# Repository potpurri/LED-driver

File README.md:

# LED Driver Board

This PCB is designed drive and dim the LED light in my hallway. It uses a LM2596 to step down the voltage from the  LED light adapter to dirve the circuit. The board also has a AMS1117-3.3 to step down the voltage to 3.3 V to be able to have an ESP-01 to turn on/off the LEDS.

## Images

### Schematic

### 3D Renderings
- Front View: 
- Back View: 

### PCB
**2-Layer Stackup**: Signal Layer, GND Layer
- All layers:

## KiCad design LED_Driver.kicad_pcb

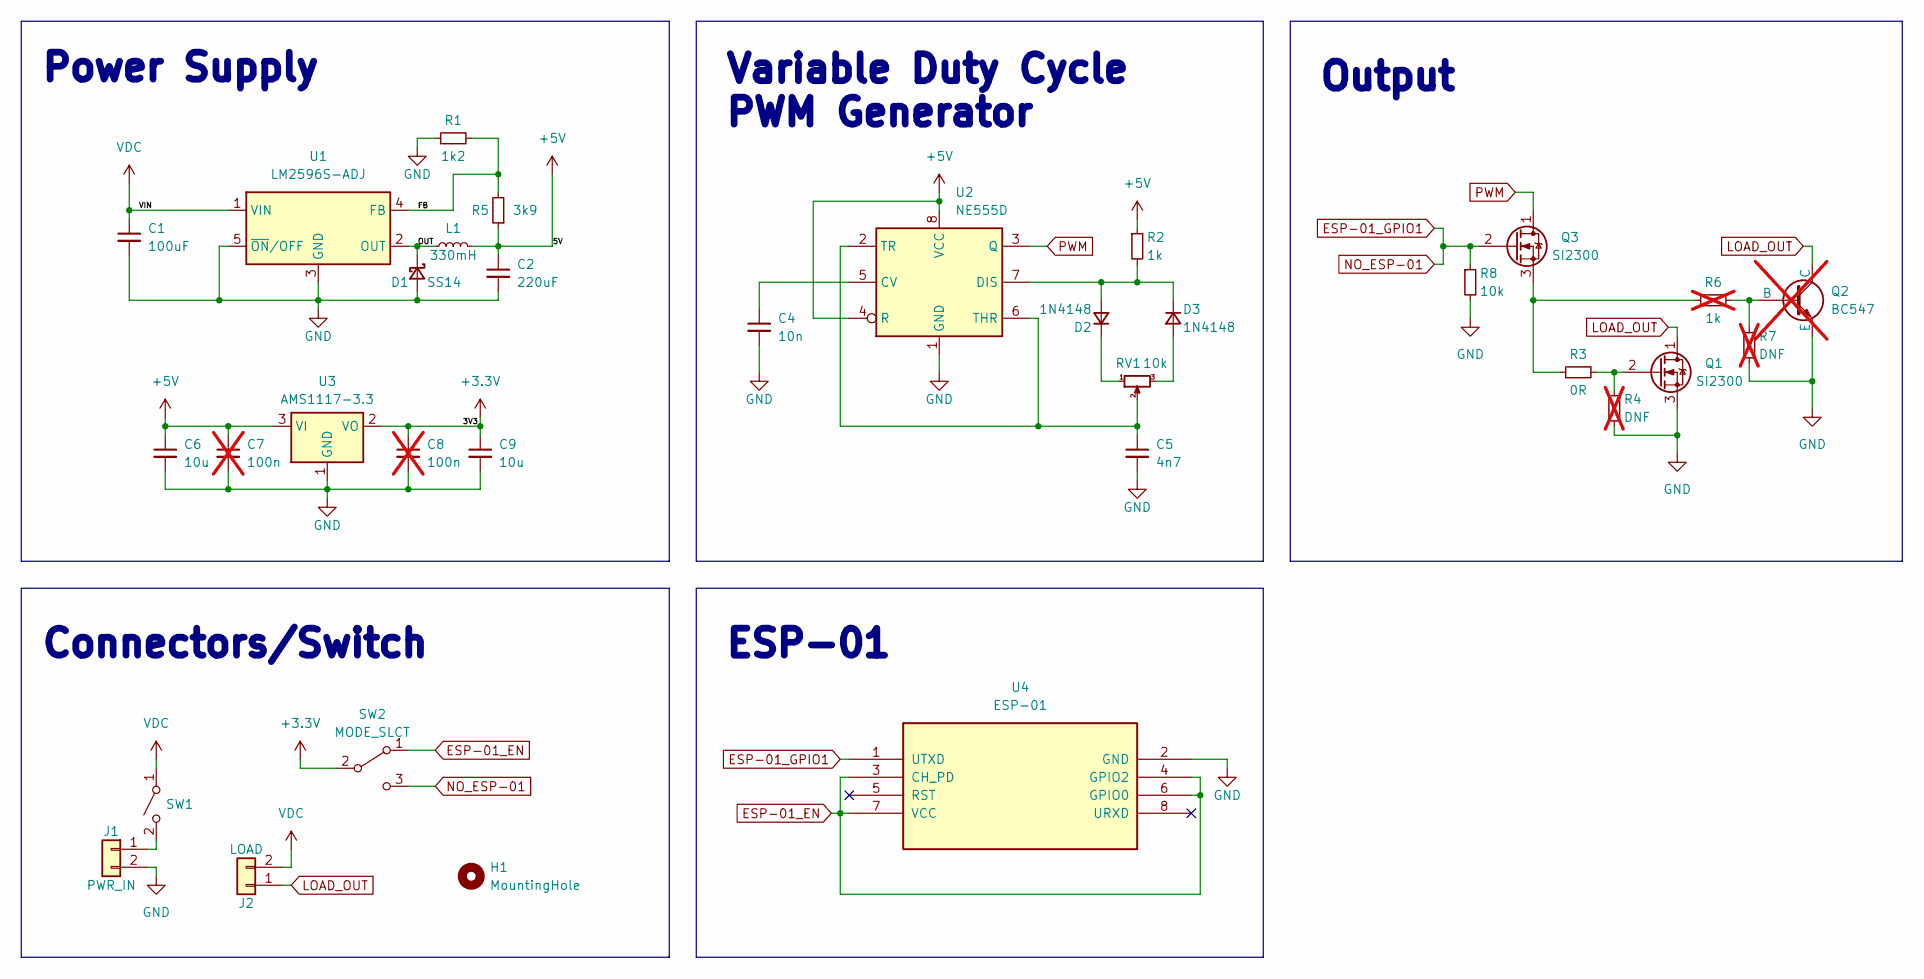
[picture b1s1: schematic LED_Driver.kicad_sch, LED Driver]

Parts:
C1: 100uF; CP_Radial_D8.0mm_P3.80mm
C2: 220uF; CP_Elec_6.3x7.7
C4: 10n; C_0603_1608Metric_Pad1.08x0.95mm_HandSolder
C5: 4n7; C_0603_1608Metric_Pad1.08x0.95mm_HandSolder
C6, C9: 10u; C_0603_1608Metric_Pad1.08x0.95mm_HandSolder
C7, C8: 100n; C_0603_1608Metric_Pad1.08x0.95mm_HandSolder; not fitted
D1: SS14; D_SMA
D2, D3: 1N4148; D_SOD-123
H1: MountingHole; MountingHole_2.5mm
J1: PWR_IN; KF350-2p
J2: LOAD; KF350-2p
L1: 330mH; L_10.4x10.4_H4.8
Q1, Q3: SI2300; SI2300 SOT-23
Q2: BC547; TO-92_HandSolder; not fitted
R1: 1k2; R_0805_2012Metric
R2: 1k; R_0805_2012Metric_Pad1.20x1.40mm_HandSolder
R3: 0R; R_0805_2012Metric
R4, R7: DNF; R_0805_2012Metric; not fitted
R5: 3k9; R_0805_2012Metric
R6: 1k; R_0805_2012Metric; not fitted
R8: 10k; R_0805_2012Metric
RV1: 10k; Potentiometer_Bourns_PTV09A-1_Single_Vertical
SW1: Switch; PinHeader_1x02_P2.54mm_Vertical
SW2: MODE_SLCT; Schiebeschalter SS-12D00
U1: LM2596S-ADJ; TO-263-5_TabPin3
U2: NE555D; SOIC-8_3.9x4.9mm_P1.27mm
U3: AMS1117-3.3; SOT-223-3_TabPin2
U4: ESP-01; PinHeader_2x04_P2.54mm_Vertical

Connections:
+3.3V: C8.1, C9.1, SW2.2 (B), U3.2 (VO)
+5V: C2.1, C6.1, C7.1, L1.2, R2.1, R5.1, U2.4 (R), U2.8 (VCC), U3.3 (VI)
/FB: R1.2, R5.2, U1.4 (FB)
/OUT: D1.1 (K), L1.1, U1.2 (OUT)
ESP-01_EN: SW2.1 (A), U4.3 (CH_PD), U4.4 (GPIO2), U4.6 (GPIO0), U4.7 (VCC)
ESP-01_GPIO1: Q3.2 (G), R8.1, SW2.3 (C), U4.1 (UTXD)
GND: C1.2, C2.2, C4.2, C5.2, C6.2, C7.2, C8.2, C9.2, D1.2 (A), J1.2, Q1.3 (S), Q2.3 (E), R1.1, R4.2, R7.2, R8.2, U1.3 (GND), U1.5 (~ON/OFF), U2.1 (GND), U3.1 (GND), U4.2 (GND); also elsewhere on the board
LOAD_OUT: J2.1, Q1.1 (D), Q2.1 (C); also elsewhere on the board
unnamed: D2.2 (A), D3.1 (K), R2.2, U2.7 (DIS)
unnamed: D2.1 (K), RV1.1
unnamed: D3.2 (A), RV1.3
unnamed 11: J1.1, SW1.2 (B); also elsewhere on the board
unnamed: Q1.2 (G), R3.2, R4.1
unnamed: Q2.2 (B), R6.2, R7.1
unnamed: Q3.3 (S), R3.1, R6.1
unnamed: C4.1, U2.5 (CV)
unnamed: C5.1, RV1.2, U2.2 (TR), U2.6 (THR)
PWM: Q3.1 (D), U2.3 (Q)
VDC: C1.1, J2.2, SW1.1 (A), U1.1 (VIN); also elsewhere on the board

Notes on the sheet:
Output
Connectors/Switch
Variable Duty Cycle PWM Generator
Power Supply
ESP-01

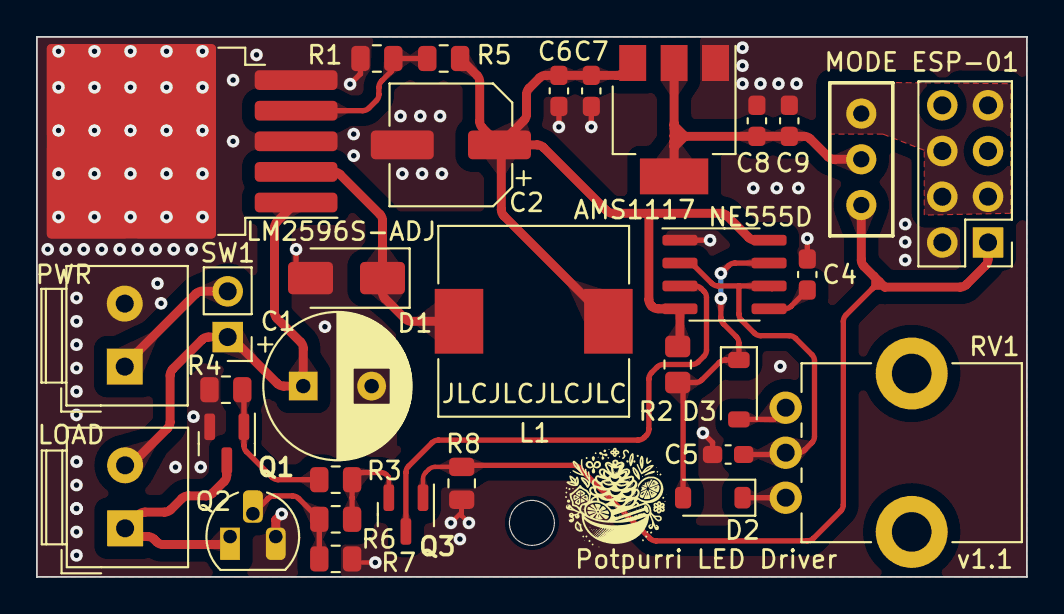
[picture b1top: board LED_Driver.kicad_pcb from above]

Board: 2 copper layers, 55.0 x 30.0 mm, 33 parts (0 on the bottom side), 19 nets.

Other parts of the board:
LOAD: LOAD; KF350-2p
PWR: PWR_IN; KF350-2p

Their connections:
GND: PWR.2; also elsewhere on the board
LOAD_OUT: LOAD.1; also elsewhere on the board
unnamed 11: PWR.1; also elsewhere on the board
VDC: LOAD.2; also elsewhere on the board

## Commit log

2024-11-15 init
2024-11-15 added readme
